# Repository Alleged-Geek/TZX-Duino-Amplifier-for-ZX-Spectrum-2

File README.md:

# TZX-Duino-Amplifier-for-ZX-Spectrum-2

This is a PCB design of an amplifier which will allow you to use a TZX Duino with a ZX Spectrum +2

Included in this repositry are the following

Gerber Files in a Zip format which can be used if you decide to get the PCB's manufactured from PCB manufacturers such as JLPCB

Eagle Brd and SCH files should you wish to modify the PCB layout in any way

A parts list which has order codes and prices from www.rapidonline.com (although as shipping is quite high from them you may find it cheaper to buy from ebay or Amazon)
the partslist and order codes will give you the actual components I used which should make it easier to find on other sites. As the minimum order for a PCB from JLPCB is 5 PCB's the parts list contains enough components for 5 fully populated PCB's

Images of the PCB layouts and schematics

I will be updating my blog with the instllaton of this PCB

check out

alleged-geek.blogspot.com for further information

I hope that you find this useful

Any questions or comments greatly appreciated

Best regards,

Alleged-Geek

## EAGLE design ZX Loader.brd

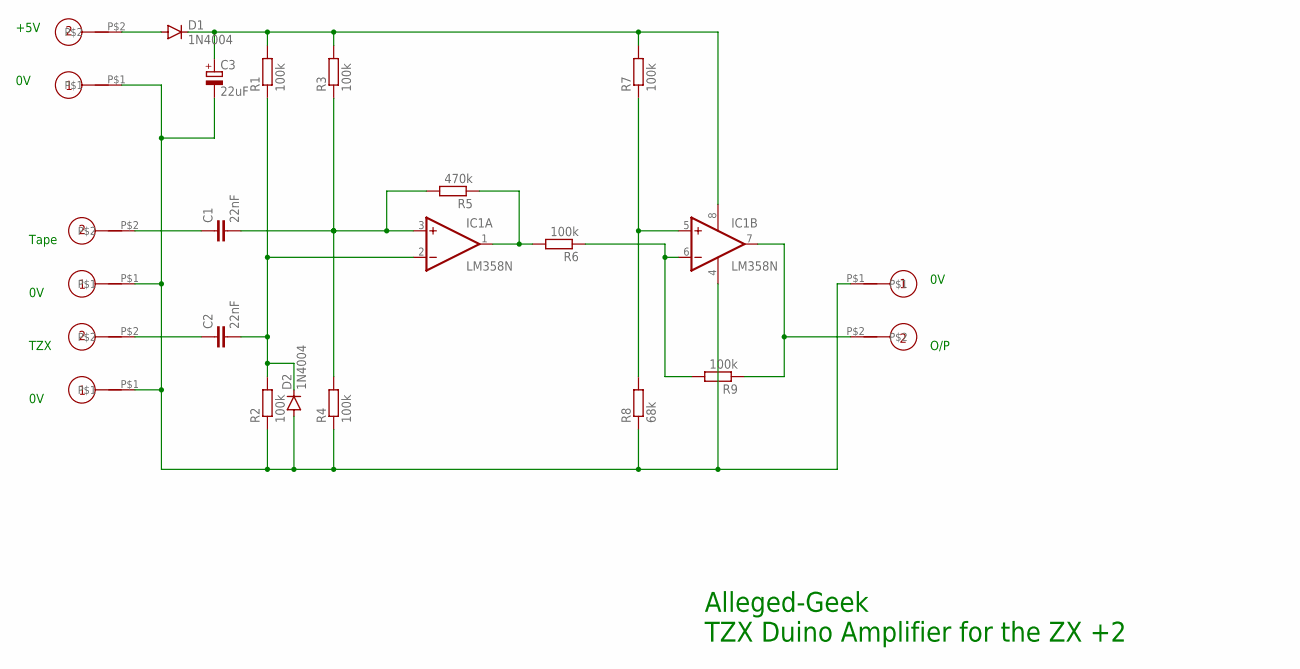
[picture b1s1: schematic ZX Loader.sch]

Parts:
C1, C2: 22nF; C050-030X075
C3: 22uF; E2,5-5
D1, D2: 1N4004; DO41-10
IC1: LM358N; DIL08
O/P: RGU-A2-PUSH-BUTTON-CONNECTOR; RGU-A2
POWER: Power; RGU-A2
R1, R2, R3, R4, R6, R7, R9: 100k; 0207/10
R5: 470k; 0207/10
R8: 68k; 0207/10
TZX: RGU-A2-PUSH-BUTTON-CONNECTOR; RGU-A2
U2: Tape; RGU-A2

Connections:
0V: C3.-, D2.A, IC1.4 (V-), O/P.P$1, POWER.P$1, R2.1, R4.1, R8.1, TZX.P$1, U2.P$1
5V: D1.A, POWER.P$2
+V: C3.+, D1.C, IC1.8 (V+), R1.2, R3.2, R7.2
EXT-I/P: C2.1, TZX.P$2
INT-I/P: C1.1, U2.P$2
unnamed: C2.2, D2.C, IC1.2 (-IN), R1.1, R2.2
unnamed: C1.2, IC1.3 (+IN), R3.1, R4.2, R5.2
unnamed: IC1.6 (-IN), R6.1, R9.2
unnamed: IC1.1 (OUT), R5.1, R6.2
unnamed: IC1.5 (+IN), R7.1, R8.2
O/P: IC1.7 (OUT), O/P.P$2, R9.1

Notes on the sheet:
+5V
O/P
TZX
Tape
Alleged-Geek TZX Duino Amplifier for the ZX +2

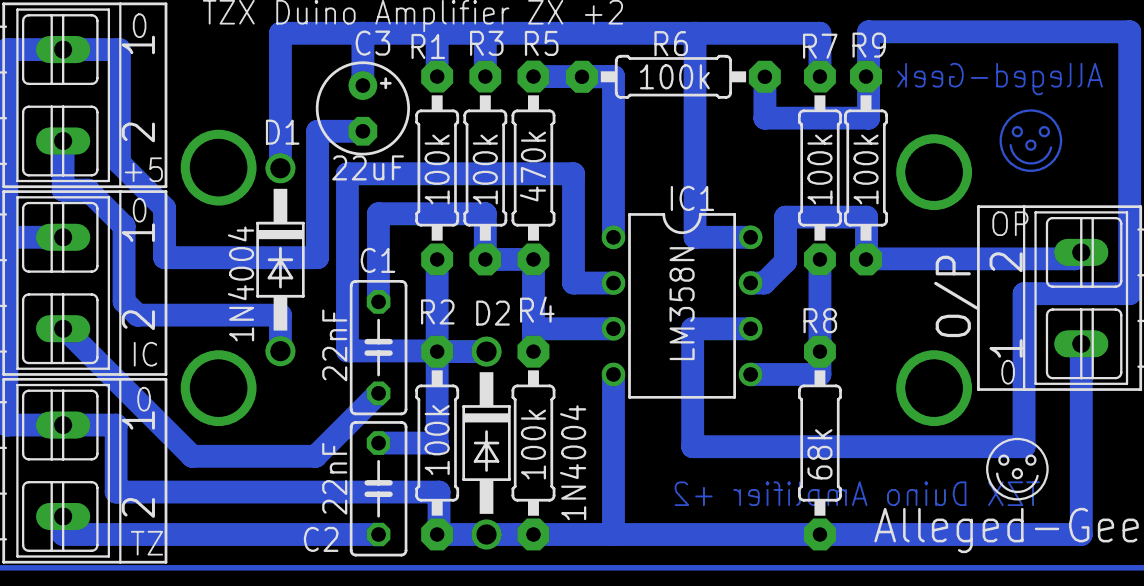
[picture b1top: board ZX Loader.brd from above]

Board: 2 copper layers, 19 parts (0 on the bottom side), 11 nets.
